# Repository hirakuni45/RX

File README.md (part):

Renesas RX Microcontroller
=========

[Japanese](READMEja.md)
   
## Overview
   
This is a program by Renesas RX microcontroller and its compiler rx-elf-gcc, g++.   
I am currently using Renesas GNU-RX gcc 8.3.0 as my main development tool.   
GNU-RX supports RXv3 and DFPU, and has excellent optimization.   

Currently, a dedicated writing program has been implemented that has been tested on Windows, OS-X, and Linux.   
Development is now possible in multiple environments.   

Currently supported and tested devices:   
|Series|MinV|MaxV|MHz|Core|FPU|TFU|DFPU|Operation check|rx_prog|Linker file|
|---|:-:|:-:|:-:|:-:|:-:|:-:|:-:|:-:|:-:|---|
|[RX110](RX110)|1.8|3.6|32|RXv1|－|－|－|||R5F51103/4/5|
|[RX111](RX111)|1.8|3.6|32|RXv1|－|－|－|||R5F51115/6/7|
|[RX113](RX113)|1.8|3.6|32|RXv1|－|－|－|||R5F51136/8|
|[RX130](RX130)|1.8|5.5|32|RXv1|－|－|－|||R5F51305/6|
|[RX140](RX140)|1.8|5.5|48|RXv2|Yes|－|－|〇|〇|R5F51403/5/6|
|[RX13T](RX13T)|2.7|5.5|32|RXv1|Yes|－|－|||R5F513T3/5|
|[RX14T](RX14T)|2.7|5.5|48|RXv2|Yes|V1|－|||R5F514T5|
|[RX210](RX210)|1.62|5.5|32|RXv1|－|－|－|||R5F52108/B|
|[RX220](RX220)|1.62|5.5|32|RXv1|－|－|－|〇|〇|R5F52206|
|[RX231](RX231)|1.8|5.5|54|RXv2|Yes|－|－|〇|〇|R5F52316/7/8|
|[RX23W](RX23W)|1.8|5.5|54|RXv2|Yes|－|－|||R5F523W7/8|
|[RX23T](RX23T)|2.7|5.5|40|RXv2|Yes|－|－|||R5F523T5|
|[RX24T](RX24T)|2.7|5.5|80|RXv2|Yes|－|－|〇|〇|R5F524T8/A|
|[RX24U](RX24U)|2.7|5.5|80|RXv2|Yes|－|－|||R5F524UB/E|
|[RX261](RX26x)|1.6|5.5|64|RXv3|Yes|－|－|〇|〇|R5F52618|
|[RX26T](RX26T)|2.7|5.5|120|RXv3|Yes|V2|－|〇|〇|R5F526TF|
|[RX621](RX62x)|2.7|3.6|100|RXv1|Yes|－|－|〇|〇|R5F56218|
|[RX62N](RX62x)|2.7|3.6|100|RXv1|Yes|－|－|〇|〇|R5F562N7/8|
|[RX631](RX63x)|2.7|3.6|100|RXv1|Yes|－|－|〇|〇|R5F5631F|
|[RX63N](RX63x)|2.7|3.6|100|RXv1|Yes|－|－|〇|〇|R5F563NE|
|[RX63T](RX63T)|3.3|5|100|RXv1|Yes|－|－|〇|〇|R5F563T6|
|[RX64M](RX64M)|2.7|3.6|120|RXv2|Yes|－|－|〇|〇|R5F564MF/G/J/L|
|[RX71M](RX71M)|2.7|3.6|240|RXv2|Yes|－|－|〇|〇|R5F571MF/G/J/L|
|[RX651](RX65x)|2.7|3.6|120|RXv2|Yes|－|－|〇|〇|R5F5651E|
|[RX65N](RX65x)|2.7|3.6|120|RXv2|Yes|－|－|〇|〇|R5F565NE|
|[RX66N](RX66N)|2.7|3.6|120|RXv3|Yes|V1|Yes|||R5F566ND/N|
|[RX660](RX660)|2.7|5.5|120|RXv3|Yes|－|－|||R5F56609|
|[RX671](RX671)|2.7|5.5|120|RXv3|Yes|－|－|||R5F5671C/E|
|[RX72N](RX72N)|2.7|3.6|240|RXv3|Yes|V1|Yes|〇|△|R5F572ND/N|
|[RX72M](RX72M)|2.7|3.6|240|RXv3|Yes|V1|Yes|△|△|R5F572MD/N|
|[RX66T](RX66T)|2.7|5.5|160|RXv3|Yes|－|－|〇|〇|R5F566TA/E/F/K|
|[RX72T](RX72T)|2.7|5.5|200|RXv3|Yes|V1|－|〇|〇|R5F572TF/K|
    
- The directory structure is updated daily.
- Some features are still under construction.
- The project consists of a Makefile and related headers and source code, and includes dedicated startup routines and linker scripts.

---
**Please make a request if you want us to support other RX devices. (Conditions below)**
- Become a support member of hirakuni45 GitHub.
- Lend us a board with the RX microcontroller you are requesting support for.
- You agree to release newly added files related to the RX microcontroller under the MIT license.

**If you do not know how to use the framework**
- Create a GitHub account and post in Discussions.
- You can also become a support member to get extensive support.

**If you have a problem with the framework or need a fix**, please create a Github account and post a note in Discussions.
- Create a Github account and post in Issues.
- If you have a modification request, post it in Discussions.
- If you have a pull request, please write the contents in Issues and Discussions in advance.

---

Space Invaders Emulator, NES Emulator, for RX65N/RX72N Envision kit   
    
WAV/MP3 Audio Player, File selector, for RX65N/RX72N Envision kit   
    
functional calculator, DX7 Emulator

YouTube: NES Emulator for RX65N Envision kit
   
Device control classes with template design patterns provide flexible and concise functionality.   
Due to its functionality, it does not require difficult or complicated settings or code generation by separate programs.   
   
```C++
// LED flashing program
#include "common/renesas.hpp"

namespace {
//  typedef device::PORT<device::PORT0, device::bitpos::B7> LED;  // LED connection port, Active HIGH
    typedef device::PORT<device::PORT0, device::bitpos::B7, false> LED;  // LED connection port, Active LOW
}

int main(int argc, char** argv);

int main(int argc, char** argv)
{
    SYSTEM_IO::boost_master_clock();

    LED::OUTPUT();
    while(1) {
        utils::delay::milli_second(250);
        LED::P = 1;
        utils::delay::milli_second(250);
        LED::P = 0;
    }
}
```
   
In order to complete the process from dependency rule generation to compilation and linking, usually with a single "make" command,
 I do not need it.   
No need for a dedicated boot program or loader I can write and execute.   
For development, we recommend using "Visual Studio Code" that can be used on multiple platforms.   
   
---

## RX Project, Library List

- For device I/O operations, dedicated headers are provided utilizing template class libraries implemented in C++.
- We also provide a full set of utilities and class libraries. 

|directory|contents|
|---|---|
|[all_project_build.sh](./all_project_build.sh)|build all projects (shell script) |
|[/RX110](./RX110)|RX110 specific device definition class, linker script|
|[/RX111](./RX111)|RX111 specific device definition class, linker script|
|[/RX130](./RX130)|RX130 specific device definition class, linker script|
|[/RX13T](./RX13T)|RX13T specific device definition class, linker script|
|[/RX14T](./RX14T)|RX14T specific device definition class, linker script|
|[/RX140](./RX140)|RX140 specific device definition class, linker script|
|[/RX210](./RX210)|RX210 specific device definition class, linker script|
|[/RX220](./RX220)|RX220 specific device definition class, linker script|
|[/RX231](./RX231)|RX231 specific device definition class, linker script|
|[/RX23W](./RX23W)|RX23W specific device definition class, linker script|
|[/RX23T](./RX23T)|RX23T specific device definition class, linker script|
|[/RX24T](./RX24T)|RX24T specific device definition class, linker script|
|[/RX24U](./RX24U)|RX24U specific device definition class, linker script|
|[/RX26x](./RX26x)|RX260/RX261 specific device definition class, linker script|
|[/RX26T](./RX26T)|RX26T specific device definition class, linker script|
|[/RX62x](./RX62x)|RX621/RX62N dedicated device definition class, linker script|
|[/RX63x](./RX63x)|RX631/RX63N specific device definition class, linker script|
|[/RX63T](./RX63T)|RX63T specific device definition class, linker script|
|[/RX64M](./RX64M)|RX64M dedicated device definition class, linker script|
|[/RX65x](./RX65x)|RX651/RX65N specific device definition class, linker script|
|[/RX660](./RX660)|RX660 specific device definition class, linker script|
|[/RX66N](./RX66N)|RX66N specific device definition class, linker script|
|[/RX66T](./RX66T)|RX66T dedicated device definition class, linker script|
|[/RX671](./RX671)|RX671 specific device definition class, linker script|
|[/RX71M](./RX71M)|RX71M dedicated device definition class, linker script|
|[/RX72N](./RX72N)|RX72N dedicated device definition class, linker script|
|[/RX72M](./RX72M)|RX72M dedicated device definition class, linker script|
|[/RX72T](./RX72T)|RX72T dedicated device definition class, linker script|
|[/RX600](./RX600)|RX microcontroller common device definition class|
|[/common](./common)|shared classes, headers, etc.|
|[/rxlib](./rxlib)|zlib, png, mad, gmp, mpfr libraries|
|[/FreeRTOS](./FreeRTOS)|FreeRTOS for various RX microcontrollers and simple samples|
|[/ff14](./ff14)|ChaN's fatfs source code and handler for RX microcontrollers|
|[/chip](./chip)|various device specific control driver libraries such as I2C, SPI, etc|
|[/graphics](./graphics)|Graphics drawing related classes|
|[/gui](./gui)|Graphics user interface related classes (GUI Widget)|
|[/sound](./sound)|sound and audio related classes|
|[/usb](./usb)|USB handler, manage class|
|[/tinyusb](./tinyusb)|TinyUSB source code|
|[/rxprog](./rxprog)|RX microcontroller, Flash program writing tool (for Windows, OS-X, Linux)
|[LICENSE](./LICENSE)|license description file|

---

## Sample Projects (Applications)

|Directory|RX220|RX631|RX63T|RX62N|RX24T|RX66T|RX72T|RX64M|RX71M|RX65N|RX72N|Contents|
|---------|:---:|:---:|:---:|:---:|:---:|:---:|:---:|:---:|:---:|:---:|:---:|---|
|[/FIRST_sample](./FIRST_sample)|〇|〇|〇|〇|〇|〇|〇|〇|〇|〇|〇|LED blinking Sample Program|
|[/SCI_sample](./SCI_sample)|〇|〇|〇|〇|〇|〇|〇|〇|〇|〇|〇|serial communication Sample Program|
|[/MTU_sample](./MTU_sample)|－|－|－|〇|〇|〇|〇|〇|〇|〇|〇|Multi-Function Timer Pulse Unit Sample Program|
|[/CAN_sample](./CAN_sample)|－|〇|－|〇|－|〇|〇|〇|〇|△|〇|CAN Communication Sample Program|
|[/FLASH_sample](./FLASH_sample)|－|－|－|－|〇|〇|〇|〇|〇|〇|〇|Internal data flash operation sample|
|[/FreeRTOS](./FreeRTOS)|〇|〇|－|〇|〇|〇|〇|〇|〇|〇|〇|FreeRTOS Basic operation sample|
|[/GPTW_sample](./GPTW_sample)|－|－|－|－|△|〇|〇|－|－|△|〇|GPTW PWM Sample Program|
|[/I2C_sample](./I2C_sample)|〇|〇|－|〇|〇|〇|〇|〇|〇|〇|〇|I2C Device Access Sample|
|[/RAYTRACER_sample](./RAYTRACER_sample)|－|〇|－|〇|〇|〇|〇|〇|〇|〇|〇|Ray Tracing Benchmark|
|[/SDCARD_sample](./SDCARD_sample)|－|－|－|－|〇|〇|〇|〇|△|〇|〇|SD Card Operation Sample|
|[/SIDE_sample](./SIDE_sample)|－|－|－|－|－|－|－|－|－|〇|〇|Envision Kit, Space Invaders emulator|
|[/NESEMU_sample](./NESEMU_sample)|－|－|－|－|－|－|－|－|－|〇|〇|Envision Kit, NES emulator|
|[/GUI_sample](./GUI_sample)|－|－|－|－|－|－|－|－|－|〇|〇|GUI Sample、Graphics User Interface (Soft rendering, using DRW2D engine)|
|[/AUDIO_sample](./AUDIO_sample)|－|－|－|－|－|－|－|〇|△|〇|〇|MP3/WAV Audio Player (FreeRTOS)|
|[/SYNTH_sample](./SYNTH_sample)|－|－|－|－|〇|〇|〇|〇|〇|〇|〇|FM sound synthesizer emulator|
|[/CALC_sample](./CALC_sample)|－|〇|－|〇|－|〇|〇|〇|〇|〇|〇|Function calculator samples (gmp, mpfr libraries)|
|[/DSOS_sample](./DSOS_sample)|－|－|－|－|－|－|－|－|－|△|〇|Digital Storage Oscilloscope Samples|
|[/PSG_sample](./PSG_sample)|－|〇|－|〇|－|〇|〇|〇|〇|〇|〇|Pseudo PSG Sound Source Performance Samples|
|[/TUSB_HOST_sample](./TUSB_HOST_sample/)|－|－|－|－|－|－|－|－|－|〇|〇|TinyUSB/Host Samples|

*Please consider directories and files that are not in the above list but exist when checked out as work in progress.

---

### rxlib directory

- Open source libraries built for RX microcontrollers

[rxlib](./rxlib) See also

---

### common directory

- Various utilities
- Convenience Classes
- Common files for each microcontrollers

[common](./common) See also

---

### chip directory

- Template driver classes for various IC manufacturers (I2C, SPI, and various other interfaces)
- In C++, the use of templates can be used to generalize operations using interfaces such as I2C and SPI.
- The headers in the chip directory are dedicated to the initialization and control of each IC and are not concerned with the interface definition.
- The context of the interface (control pins) is given by reference.
- Since there is no definition of interfaces, the creation is very versatile and highly flexible.

[chip](./chip) See also

---

### graphics directory

 - Classes related to screen rendering

[graphics](./graphics) See also

---

### gui directory

- GUI Widget Classes

[gui](./gui) See also

---

### sound directory

 - Classes related to sound

[sound](./sound) See also

---

### ff14 directory

- Mr. ChaN's FatFs source code set
- MMC Driver Class (SPI)
- If SDHI interface is available, real mode driver can also be selected.

[ff14](./ff14) See also

---

### KiCAD directory

- For KiCAD, parts files, etc.

[KiCAD_lib](./KiCAD_lib) See also

---

### legacy directory

- Files not currently supported, etc.

[legacy](./legacy) See also

---

## Installation and Feature Overview of Renesas GNU-RX (14.2.0-202607)

[Open Source Tools for Renesas](https://llvm-gcc-renesas.com/ja/) provides GNU tools for RX microcontrollers.

The latest (as of July 2026) GNU toolchain for RX microcontrollers—
- gcc 14.2.0 [released]
- binutils 2.44 [released]
- newlib 4.4.0 [released]
- gdb 16.2 [released]

A toolchain for RX microcontrollers based on these components is available for download.

Anyone can download these tools by registering, and there are no size limits.
Additionally, it appears they provide optimization for RX microcontrollers and support for the latest CPU cores.

**When installing, we recommend selecting “Available to all users”**

- Since gcc is based on version 14.2.0, it supports C++17
- It offers deeper optimization than standard gcc and supports the latest CPU cores
- All projects using the C++ frameworks published here can be compiled
- Experimental support for C++20 and C++26 features has been added
- Support is also provided by CyberTHOR Studios Limited
- To use this tool with MSYS2, after installing the toolchain, please set the command path in `.bash_profile`
- When compiling open-source libraries, there is an issue where the path string may contain “spaces” or double-byte characters
- To work around this issue, it is recommended to copy the directory to “/usr/local” and use that path
- Based on gcc-14, the installation directory has changed (when installed for use by all users)

```bash
# rx-elf path
# PATH=$PATH:/usr/local/rx-elf/bin
PATH=$PATH:/C/ProgramData/'GCC for Renesas RX 14.2.0.202607-GNURX-ELF'/rx-elf/rx-elf/bin
```

- RXv3 core support
- Generation of double-precision floating-point instructions for RX72N/RX72M
- Support for the built-in TFU (trigonometric function unit) in RX14T/RX26T/RX72T/RX72N/RX72M (V1/V2)

### Compiler options for TFUv1 and TFUv2

Starting with the gcc-14.2.0 base, the handling of the TFU has changed

```sh
TFUv1:
  -mtfu-version=v1 -mtfu=intrinsic,mathlib

TFUv2:
  -mtfu-version=v2 -mtfu=intrinsic,mathlib
```

These settings are configured in common/makefile

- The built-in functions differ between TFUv1 and TFUv2, so please be careful when using TFU
- When TFU usage is specified, the built-in variable “__TFU” is set to “TFUv1: 1” or “TFUv2: 2”

---

The difference between CC-RX:   
In terms of compiler optimization, CC-RX seems to be superior to GNU-RX in the CoreMark benchmark.   
It's hard to imagine why such a big difference would occur, but if you know the internal structure of the CPU, you might be able to achieve it...   
   
|Compiler|RX core|CoreMark (MHz)|Rate|
|---|:-:|:-:|:-:|
|CC-RX (V3.02)|RX72N|5.21|1.00|
|GNU-RX (8.3.x)|RX72N|3.59|0.69|
|||||
|CC-RX (V3.02)|RX65N|4.37|1.00|
|GNU-RX (8.3.x)|RX65N|3.22|0.74|
   
The above values are quite exciting, but when running actual applications, we do not feel such a big difference in sensory perception.   
- The big difference seems to occur in the case of applications that use a lot of instructions that require a relatively large number of CPU cycles, such as multiplication and division.   
- For applications that use a lot of floating point instructions, GNU-RX may be faster.
   
No matter how good CC-RX is, it's not worth the cost for hobbyists, and if it doesn't support C++11, it's not practical to use.   
In addition, the above benchmarks are based on CoreMark, so you need to evaluate it with actual applications to know what it really is.   
   
---
## RX Development environment preparation (Windows、MSYS2)
   
 - On Windows, install the MSYS2 environment in advance.   
 - MSYS2 has msys2, mingw32, mingw64 and 3 different environments, but gcc for RX microcontroller
   Because it is necessary to build of, do with msys2.   
1. MSYS2 is a UNIX-based application development environment.
2. MINGW32 is an environment for i686 that the exception model of gcc is not war related to SEH because of Borland patent.
3. MINGW64 is an environment for developing Windows-based applications.   
 - If you have installed any software other than Microsoft's anti-virus software, please disable it.
1. The GCC build may take an unusually long time or may fail to build.   

 - MSYS2 upgrade

```bash
   pacman -Sy pacman
   pacman -Syu
```
   
- Open the console again. (You should see a message as you reopen the console)   
   
```bash
   pacman -Su
```
- The update is done multiple times, then follow the instructions on the console.
- You need to reopen the console several times.

- Install gcc, texinfo, gmp, mpfr, mpc, diffutils, automake, zlib, tar, make, unzip, git commands etc
```bash
   pacman -S gcc
   pacman -S texinfo
   pacman -S mpc-devel
   pacman -S diffutils
   pacman -S automake
   pacman -S zlib
   pacman -S tar
   pacman -S make
   pacman -S unzip
   pacman -S zlib-devel
   pacman -S git
```
   
---
## RX Development environment preparation (OS-X)
   
- In OS-X, install macports in advance.   
  brew is not recommended because it has less flexibility   
- Depending on the version of OS-X, you may need to install X-Code, Command Line Tools, etc. in advance   
 - macports upgrade   
```bash
   sudo port -d self update
```
- As you probably know, in the early stage of OS-X, llvm starts by calling gcc.
- However, llvm can not currently build gcc cross compilers.
- So, I will install gcc on macports, I will use the 5 series version.
```bash
   sudo port install gcc5
   sudo ln -sf /opt/local/bin/gcc-mp-5  /usr/local/bin/gcc
   sudo ln -sf /opt/local/bin/g++-mp-5  /usr/local/bin/g++
   sudo ln -sf /opt/local/bin/g++-mp-5  /usr/local/bin/c++
```
- You may need to reboot.
- For now, please check.
```bash
   gcc --version
```
   
```bash
   gcc (MacPorts gcc5 5.4.0_0) 5.4.0
   Copyright (C) 2015 Free Software Foundation, Inc.
   This is free software; see the source for copying conditions.  There is NO
   warranty; not even for MERCHANTABILITY or FITNESS FOR A PARTICULAR PURPOSE.
```
   
 - Install texinfo, gmp, mpfr, mpc, diffutils, automake command etc
```bash
   sudo port install texinfo
   sudo port install gmp
   sudo port install mpfr
   sudo port install libmpc
   sudo port install diffutils
   sudo port install automake
```
   
---
## RX Development environment preparation (Ubuntu)

- There are multiple Linux environments, so here we will write the case for the "Ubuntu 16.04 LTS" environment.
   
- Install texinfo, gmp, mpfr, mpc, diffutils, automake command etc
```bash
   sudo apt-get install texinfo
   sudo apt-get install libgmp-dev
   sudo apt-get install libmpfr-dev
   sudo apt-get install libmpc-dev
   sudo apt-get install diffutils
   sudo apt-get install automake
   sudo apt-get install zlib1g-dev
```
   
---
## RX Development environment construction
   
- The RX compiler (rx-elf-gcc, g++) uses "gcc-7.5.0".   
- Download "binutils-2.34.tar.gz".   
- Download "gcc-7.5.0.tar.gz".   
- Download "newlib-2.4.0.tar.gz".   
- There are multiple versions of binutils, gcc and newlib, but some combinations   
  It has been found that ineligible binaries (which have subtle problems with operation) will be built.
- This bug occurs when using Renesas network stack (net_T4).
- It is not possible to identify the cause why such malfunction occurs.
- Here is a list of combinations that we have investigated.
```
   binutils-2.27, gcc-4.9.4, newlib-2.2.0 ---> OK
   binutils-2.27, gcc-5.5.0, newlib-2.2.0 ---> OK
   binutils-2.27, gcc-5.5.0, newlib-2.4.0 ---> OK
   binutils-2.27, gcc-6.4.0, newlib-2.4.0 ---> OK
   binutils-2.28, gcc-6.4.0, newlib-2.4.0 ---> OK
   binutils-2.30, gcc-6.4.0, newlib-2.4.0 ---> OK (old current)
   binutils-2.30, gcc-6.4.0, newlib-3.0.0 ---> NG
   binutils-2.34, gcc-7.5.0, newlib-2.4.0 ---> OK (new current)
```
- Using the latest gcc seems to be faster code, especially for C++.
   
---
#### build binutils-2.34
```bash
   cd
   tar xfvz binutils-2.34.tar.gz
   cd binutils-2.34
   mkdir rx_build
   cd rx_build
   ../configure --target=rx-elf --prefix=/usr/local/rx-elf --disable-nls
   make
   make install     OS-X,Linux: (sudo make install)
```

-  Pass PATH to /usr/local/rx-elf/bin (edit .bash_profile and add path)

```bash
   PATH=$PATH:/usr/local/rx-elf/bin
```

- Open the console again.

```bash
   rx-elf-as --version
```

- Execute the assembler command and check if the path is valid.
  
#### Build C compiler
```bash
    cd
    tar xfvz gcc-7.5.0.tar.gz
    cd gcc-7.5.0
    mkdir rx_build
	cd rx_build
    ../configure --prefix=/usr/local/rx-elf --target=rx-elf --enable-languages=c --disable-libssp --with-newlib --disable-nls --disable-threads --disable-libgomp --disable-libmudflap --disable-libstdcxx-pch --disable-multilib --enable-lto
    make
    make install     OS-X,Linux: (sudo make install)
```
  
#### Build newlib
```bash
    cd
    tar xfvz newlib-2.4.0.tar.gz
	cd newlib-2.4.0
    mkdir rx_build
    cd rx_build
    ../configure --target=rx-elf --prefix=/usr/local/rx-elf
	make
    make install     OS-X: (sudo make install)
```
- In Linux environment, sudo command does not recognize the path of binutils set up locally.
"Make install" will fail, so write the following script and execute it.
```bash
#!/bin/sh
# file: rx_install.sh

PATH=${PATH}:/usr/local/rx-elf/bin
make install
```
   
```bash
    sudo rx_install.sh
```
   
#### Build C++ compiler
```bash
    cd
    cd gcc-7.5.0
    cd rx_build
    ../configure --prefix=/usr/local/rx-elf --target=rx-elf --enable-languages=c,c++ --disable-libssp --with-newlib --disable-nls --disable-threads --disable-libgomp --disable-libmudflap --disable-libstdcxx-pch --disable-multilib --enable-lto --with-system-zlib
    make
    make install     OS-X,Linux: (sudo make install)
```
---
   
 - The built compiler collection is listed in the link below. (MSYS2 only)   
http://www.rvf-rc45.net/Renesas_GNU_Tools/ 

---
## Get RX Framework Source Code
```bash
    git clone https://github.com/hirakuni45/RX.git
```
   
---
### Boost installation used by RX framework

- In the past, boost was installed for mingw64 using pacman in the MSYS2 environment.
- However, as the version of boost advanced, we found that this boost caused problems.
- Therefore, we put the boost archive in the proper location and handle it.
- This method is used in the MSYS2 environment.
- Since boost uses 1.74.0, please download it in advance (place it in D:³ Download). (boost_1_74_0.tar.gz)

```bash
cd /c/
tar xfvz /d/Download/boost_1_74_0.tar.gz
```

---
## RX Build all projects
```bash
    sh all_project_build.sh [clean]
```
--- 
## How to write program to RX microcontroller

There are several ways, but the easiest and least expensive way is to use the serial interface
It is a method of writing.   
- However, the writing speed is not very fast.   
   
In case of RX microcontroller with built-in USB interface, you can boot and connect with USB, but the driver Seems to only support the Windows version.
- The circumstances around here may be wrong as we have not investigated in detail.   
   
The most common, because not all RX microcontrollers have built-in USB interface We will show you how to write using serial interface.
   
- Writing at the serial interface is reasonably fast but easy and secure, and easy to connect.   
   
- The hardware manual describes the connection with the serial port and switching to boot mode.
  Please refer to it.   
- Normally, setting MD terminal to L or H allows switching between program and internal ROM execution.   
- It is also necessary to control the state of the UB terminal.   
- If you use a USB serial conversion module etc., it is easy to get power.   

1. RXD serial reception   
2. TXD serial transmission   
3. VCC power (5V or 3.3V)   
4. GND power 0V   
- As 3.3V can only extract a limited current, a regulator is always required.   
- Details on the connection method, boot mode settings, etc. can be found in the hardware manual for each device.   
   
## Construction of flash programmer for RX microcontroller
- Currently, flash writing to RX63T, RX24T, RX64M, and RX71M is confirmed.
- Since the reset is not controlled, it is necessary to assert the reset signal at the time of writing.
- In the current version, only erase, write and compare operations are implemented.
- Code protection ID settings and operations are not implemented yet.
- In the RX24T and RX63T, the erase operation is ignored because the erase is performed automatically when the connection is established.
   
- Build rxprog in MSYS2 environment.
- Copy the built executable file to "/usr/local/bin".
- Pass the PATH to /usr/local/bin.
```bash
    cd rxprog
    make
    make install
```
```
Renesas RX Series Programmer Version 0.90b
Copyright (C) 2016,2018 Hiramatsu Kunihito (hira@rvf-rc45.net)
usage:
rx_prog [options] [mot file] ...

Options :
    -P PORT,   --port=PORT     Specify serial port
    -s SPEED,  --speed=SPEED   Specify serial speed
    -d DEVICE, --device=DEVICE Specify device name
    -e, --erase                Perform a device erase to a minimum
    -v, --verify               Perform data verify
    -w, --write                Perform data write
    --progress                 display Progress output
    --device-list              Display device list
    --verbose                  Verbose output
    -h, --help                 Display this
```
- Edit rx_prog.conf and set the COM port to connect and the baud rate.
- Ports and baud rates can be set for each of Windows, OS-X and Linux environments.
- You can write a standard serial port in "rx_prog.conf", and you should set it according to your environment.
- Each project's "Makefile" contains a script that can be written using "make run".
   
rx_prog.conf:
```
port_win   = COM12
port_osx   = /dev/tty.usbserial-DA00X2QP
port_linux = /dev/ttyUSB0
speed_win = 230400
speed_osx = 230400
speed_linux = 230400
```
---
## Development using Renesus RX72N Envision Kit

---
## Programming environment using C++ framework
   
- The following is an example program to communicate with SCI in C++.   
1. The port of SCI is defined by "port_map.hpp", and there is more than one port to select
There is no need to make complicated settings if you set "second candidate" or "third candidate".   
2. The baud rate can be set as an integer, and is automatically calculated internally from the set frequency.   
3. Even if you use interrupts, you can use them without polling (polling).   
4. Transmission and reception are performed through a fixed length FIFO class, and the size can be freely defined.   
5. The sci_putch and sci_getch functions are called from POSIX file functions, so they can be linked externally.   
6. The above functions are accessed from stdout, stdin, stderr descriptors, so you can also use the printf function, but for various reasons we do not recommend using "utils :: format", which is the size It is smaller, more flexible, convenient and safe.   
```C++
#include "common/renesas.hpp"
#include "common/fixed_fifo.hpp"
#include "common/sci_io.hpp"
#include "common/format.hpp"

namespace {
//  Use SCI9
    typedef device::SCI9 SCI_CH;

    typedef utils::fixed_fifo<char, 512> RXB;  // RX (RECV) buffer definition at 512 bytes
    typedef utils::fixed_fifo<char, 256> TXB;  // TX (SEND) buffer definition at 256 bytes

    typedef device::sci_io<SCI_CH, RXB, TXB> SCI;
//    When selecting a second candidate for the SCI port
//    typedef device::sci_io<SCI_CH, RXB, TXB, device::port_map::option::SECOND> SCI;
    SCI     sci_;
}

extern "C" {
    // standard output, called from "syscalls.c"（stdout, stderr）
    void sci_putch(char ch) { sci_.putch(ch); }

    void sci_puts(const char* str) { sci_.puts(str); }

    // standard input, called from "syscalls.c"（stdin）
    char sci_getch(void) { return sci_.getch(); }

    uint16_t sci_length() { return sci_.recv_length(); }
}

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
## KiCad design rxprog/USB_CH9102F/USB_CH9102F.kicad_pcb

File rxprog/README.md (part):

Renesas RX microcontroller flash programming tool (rx_prog)
=========

[Japanese](READMEja.md)

## Overview
Tool to write program to flash memory of RX microcontroller using serial interface   
   
|RX Microcontroller|Support|operation verification|
|:-:|:-:|:-:|
|RX13T|〇|ー|
|RX140|〇|〇|
|RX220|〇|〇|
|RX230|〇|ー|
|RX231|〇|〇|
|RX23T|〇|ー|
|RX24T|〇|〇|
|RX24U|〇|ー|
|RX260/RX261|〇|ー|
|RX26T|〇|〇|
|RX621/RX62N|〇|〇|
|RX631/RX63N|〇|〇|
|RX63T|〇|〇|
|RX64M|〇|〇|
|RX651/RX65N|〇|ー|
|RX66T|〇|〇|
|RX71M|〇|〇|
|RX72T|〇|〇|
|RX72N|〇|ー|
   
---
   
## Project list
   
- main.cpp
- conf_in.hpp
- file_io.cpp
- file_io.hpp
- format.hpp
- motsx_io.hpp
- protocol_base.hpp
- rs232c_io.hpp
- rx_prog.hpp
- rx_protocol.hpp
- rx220_protocol.hpp
- rx23x_protocol.hpp
- rx24t_protocol.hpp
- rx26t_protocol.hpp
- rx62x_protocol.hpp
- rx63x_protocol.hpp
- rx64m_protocol.hpp
- rx65x_protocol.hpp
- rx66t_protocol.hpp
- rx72t_protocol.hpp
- sjis_utf16.cpp
- sjis_utf16.hpp
- string_utils.cpp
- string_utils.hpp
- Makefile
- rx_prog.conf
- /USB_CH9102F
- /USB_CP2102N
   
---
   
## Preparation of build (compilation) environment (Windows)
   
- MSYS2 setup
- gcc related installation (C++20)
- With C++20 support, Boost is no longer required
   
See development environment preparation of 'RX/README.md'
   
---
   
## Build method, environment setting
   
- make
- Copy configuration file and executable file by make install
- pass the path to '/usr/local/bin'
   
---
   
## Connection preparation (serial connection)
   
- Connect the VSS pin of the microcontroller to the GND of USB serial.
- Connect the RXD1 pin on the microcontroller side with the USB serial TXD.
- Connect the TXD1 pin on the microcontroller side with the USB serial RXD.
※SCI port at boot (usually SCI1, hardware manual for confirmation)   
- Pull down if the device has a UB terminal. (4.7K)
- Pull down if there is an EMLE terminal. (4.7K)
- Set the MD terminal to "Low" and input the "Reset" signal.
- When executing an internal program, set the MD pin to "High level" and input reset signal.
- MDE(13) is 0 (assumed little-endian)

---

## Connection terminal list

### RX140:

|Terminal|LFQFP 64|
|---|---|
|MD|MD(3)|
|RXD|P30/RXD1(14)|
|TXD|P26/TXD1(16)|

|Mode|MD|
|---|:---:|
|Serial Boot|0|
|Single Chip|1|

VCL: 4.7uF

### RX220:
|Terminal|LFQFP 64|
|---|---|
|MD|MD(3)|
|B/UB|PC7(27)|
|RXD|P30/RXD1(14)|
|TXD|P26/TXD1(16)|

|Mode|B/UB|MD|
|---|:---:|:---:|
|Boot Mode|0|0|
|User Boot Mode|1|0|
|Single Chip|-|1|

VCL: 0.1uF

---
### RX231:   
|Terminal|LFQFP 64|LFQFP 100|
|---|---|---|
|MD|MD(3)|MD(7)|
|UB|PC7(27)|PC7(45)|
|RXD|P30/RXD1(14)|P30/RXD1(20)|
|TXD|P26/TXD1(16)|P25/TXD1(23)|

|Mode|UB|MD|
|---|:---:|:---:|
|Serial Boot|0|0|
|USB Boot|1|0|
|Single Chip|-|1|

VCL: 4.7uF

---
### RX621/RX62N:
|Terminal|RX621/RX62N (144)|
|---|---|
|MD0|MD0(16)|
|MD1|MD1(15)|
|EMLE|EMLE(10)|
|RXD|P30/RXD1(29)|
|TXD|P26/TXD1(31)|
   
|Mode|MD0|MD1|
|---|:---:|:---:|
|Serial Boot|1|0|
|USB Boot|0|1|
|Single Chip|1|1|

VCL: 0.1uF

---
### RX631/RX63N:
|Terminal|LQFP 48|LQFP 64|TFLGA 64|LQFP 100|TFLGA 100|LQFP 144|TFLGA 145|LQFP 176|LFBGA 176|TFLGA 177|
|---|---|---|---|---|---|---|---|---|---|---|
|UB|PC7(21)|PC7(27)|PA6(D5)|PC7(45)|PC7(H7)|PC7(60)|PC7(N9)|PC7(76)|PC7(N10)|PC7(N10)|
|MD|MD/FINED(2)|MD/FINED(3)|MD/FINED(C2)|MD/FINED(7)|MD/FINED(D3)|MD/FINED(16)|MD/FINED(G3)|MD/FINED(18)|MD/FINED(G3)|MD/FINED(G3)|
|EMLE|-|EMLE(1)|EMLE(C3)|EMLE(2)|EMLE(B1)|EMLE(10)|EMLE(E4)|EMLE(10)|EMLE(E2)|EMLE(E2)|
|RXD|P30/RXD1(10)|P30/RXD1(14)|P30/RXD1(E3)|P30/RXD1(20)|P30/RXD1(G3)|P30/RXD1(29)|P30/RXD1(J4)|PF2/RXD1(31)|PF2/RXD1(K3)|PF2/RXD1(K3)|
|TXD|P26/TXD1(12)|P26/TXD1(16)|P26/TXD1(G2)|P26/TXD1(22)|P26/RXD1(H1)|P26/RXD1(31)|P26/RXD1(K2)|PF0/RXD1(35)|PF0/RXD1(L3)|PF0/RXD1(L3)|

|Mode|UB|MD|
|---|:---:|:---:|
|Serial Boot|0|0|
|USB Boot|1|0|
|Single Chip|-|1|

VCL: 0.1uF

---
### RX63T/RX24T/RX26T/RX66T/RX72T:
|Terminal|RX63T (64)|RX24T (100)|RX26T (100)|RX66T (100)|RX72T (144)|
|---|---|---|---|---|---|
|VCL|0.1uF|4.7uF|0.47uF|0.47uF|0.47uF|0.47uF|
|UB|P00(2)|ー|ー|UB/P00(4)|UB/P00(9)|
|MD|MD(5)|MD(6)|MD/FINED(6)|MD/FINED(6)|MD/FINED(11)|
|EMLE|EMLE(1)|ー|EMLE(2)|EMLE(2)|EMLE(7)|
|RXD|PD5/RXD1(14)|PD5/RXD1(20)|PD5/RXD1(20)|PD5/RXD1(20)|PD5/RXD1(25)|
|TXD|PD3/TXD1(16)|PD3/TXD1(22)|PD3/TXD1(22)|PD3/TXD1(22)|PD3/TXD1(27)|

|Mode|UB|MD|
|---|:---:|:---:|
|Serial Boot|0|0|
|USB Boot|1|0|
|Single Chip|-|1|

---
### RX64M/RX71M/RX651/RX65N:
|Terminal|RX64M (176)|RX71M (176)|RX651/RX65N (176)|
|---|---|---|---|
|VCL|0.1uF|0.22uF|0.22uF|
|UB|PC7/UB(76)|PC7/UB(76)|PC7/UB(76)|
|MD|MD/FINED(18)|MD/FINED(18)|MD/FINED(18)|
|EMLE|EMLE(10)|EMLE(10)|EMLE(10)|
|RXD|PF2/RXD1(31)|PF2/RXD1(31)|PF2/RXD1(31)|
|TXD|PF0/TXD1(35)|PF0/TXD1(35)|PF0/TXD1(35)|
   
|Mode|UB|MD|
|---|:---:|:---:|
|Serial Boot|0|0|
|USB Boot|1|0|
|Single Chip|-|1|

---
### RX660/RX671:
|Terminal|RX660 (144)|RX671 (144)|
|---|---|---|
|UB|PC7/UB(60)|PC7/UB(60)|
|MD|MD/PN6(16)|MD(16)|
|RXD|P30/RXD1(29)|P30/RXD1(29)|
|TXD|P26/TXD1(31)|P26/TXD1(31)|

RX660:
|Mode|UB|MD|
|---|:---:|:---:|
|Serial Boot|0|0|
|User Boot|1|0|
|Single Chip|-|1|

VCL: 0.47uF

RX660: USB boot not available due to lack of USB interface

RX671:
|Mode|UB|MD|
|---|:---:|:---:|
|Serial Boot|0|0|
|USB Boot|1|0|
|Single Chip|-|1|

VCL: 0.22uF

---
   
- MD0、MD1、UB、MD、B/UB, and EMLE terminals are pulled up or down with a resistor (approximately 4.7K).
- Connect appropriate crystals to XTAL and EXTAL.
- Connect the specified capacitor to VCL.
- Connect all the power supplies such as VSS, VCC, AVSS, AVCC etc.
- Connect USB power sources such as USB_VSS and USB_VCC properly.
   
※For details, refer to the hardware manual for each device, "Overview, Pin Assignment", "Flash Memory, Boot Mode".   
※The circuit diagram of the Renesas board is available for reference.   
   
---
## Method of operation

### Confirm start of rx_prog
 - Run rx_prog and verify that it works (help is listed)
```
% rx_prog
Renesas RX Series Programmer Version 1.98
Copyright (C) 2016, 2026 Hiramatsu Kunihito (hira@rvf-rc45.net)
usage:
rx_prog [options] [mot file] ...

Options :
    -P PORT,   --port=PORT     Specify serial port
    -s SPEED,  --speed=SPEED   Specify serial speed
    -d DEVICE, --device=DEVICE Specify device name
    -e, --erase                Perform a device erase to a minimum
    --id=ID[:,]ID[:,] ...      Specify protect ID (16 bytes)
    -r, --read                 Perform data read
	--area=ORG[:,]END          Specify read area
    -v, --verify               Perform data verify
    -w, --write                Perform data write
    --progress                 display Progress output
    --erase-page-wait=WAIT     Delay per read page  (2000) [uS]
    --write-page-wait=WAIT     Delay per write page (5000) [uS]
    --device-list              Display device list
    --verbose                  Verbose output
    -h, --help                 Display this
```
   
### rx_prog.conf settings
 - Describe the settings of each device, port, baud rate, and so on.
 - You can specify the serial device port path individually so that settings can be shared between platforms.
 - Set the port name, baud rate, etc. according to your environment.
 - For the RX62x, the error is limited to 115200 for high baud rates.
   
rx_prog.conf configuration example
```
# Standard serial port, platform dependent port name
# port_win, port_osx and port_linux are recognized by platform and take precedence over port.
#port = /dev/ttyS10
#port = COM12
port_win   = COM3
port_osx   = /dev/tty.usbserial-DA00X2QP
port_linux = /dev/ttyUSB0

# Standard serial speed, platform dependent speed
# speed_win, speed_osx and speed_linux are recognized by platform and take precedence over speed.
# ※The maximum speed that can be set varies depending on the platform.
#speed = 230400
speed_win = 230400
speed_osx = 230400
speed_linux = 230400

# erase-page command wait [uS]
erase_page_wait = 2000
# write-page command wait [uS]
write_page_wait = 5000
```
rx_prog.conf is scanned and loaded in the following order:   
- Current directory
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
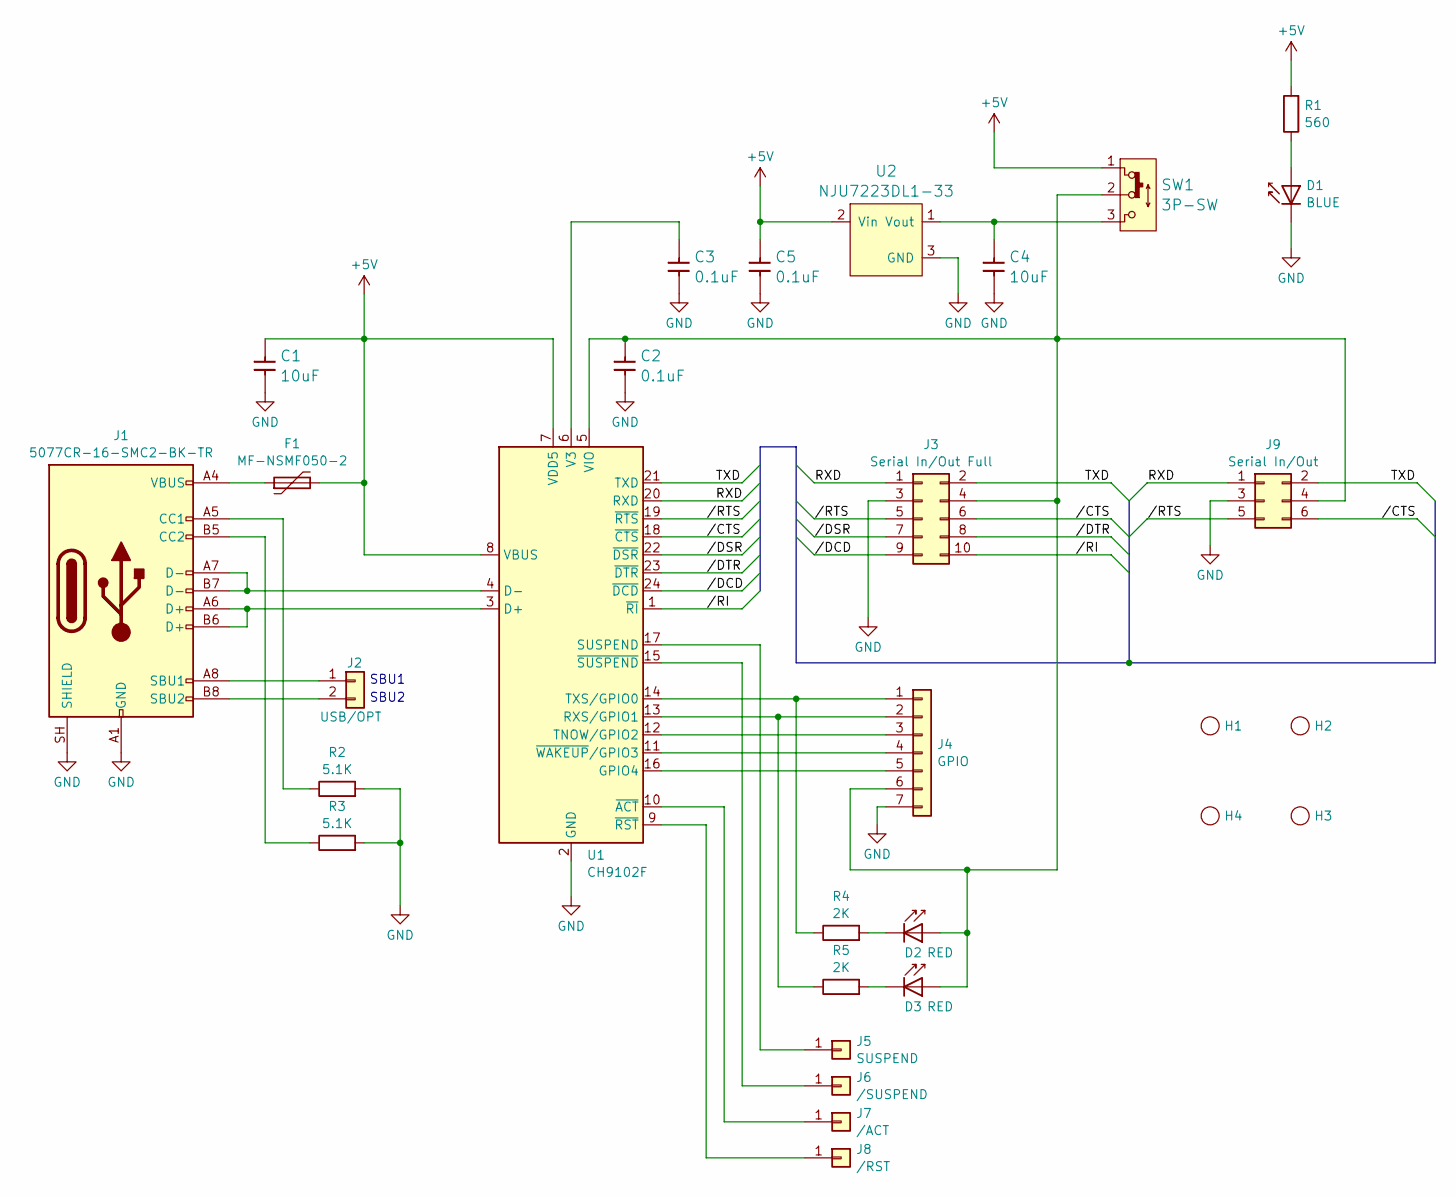
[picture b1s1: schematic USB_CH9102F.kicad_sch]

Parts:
C1, C4: 10uF; C_0603_1608Metric_Pad1.08x0.95mm_HandSolder
C2, C3, C5: 0.1uF; C_0603_1608Metric_Pad1.08x0.95mm_HandSolder
D1: BLUE; LED_0805_2012Metric_Pad1.15x1.40mm_HandSolder
D2, D3: RED; LED_0603_1608Metric_Pad1.05x0.95mm_HandSolder
F1: MF-NSMF050-2; Fuse_1206_3216Metric_Pad1.42x1.75mm_HandSolder
H1, H2, H3, H4: Hole3.2mm
J1: 5077CR-16-SMC2-BK-TR; USB_C_Receptacle_HCTL_HC-TYPE-C-16P-01A
J2: USB/OPT; PinHeader_1x02_P2.54mm_Vertical
J3: Serial In/Out Full; IDC-Header_2x05_P2.54mm_Vertical
J4: GPIO; PinHeader_1x07_P2.54mm_Vertical
J5: SUSPEND; PinHeader_1x01_P2.54mm_Vertical
J6: /SUSPEND; PinHeader_1x01_P2.54mm_Vertical
J7: /ACT; PinHeader_1x01_P2.54mm_Vertical
J8: /RST; PinHeader_1x01_P2.54mm_Vertical
J9: Serial In/Out; IDC-Header_2x03_P2.54mm_Vertical
R1: 560; R_0603_1608Metric_Pad0.98x0.95mm_HandSolder
R2, R3: 5.1K; R_0603_1608Metric_Pad0.98x0.95mm_HandSolder
R4, R5: 2K; R_0603_1608Metric_Pad0.98x0.95mm_HandSolder
SW1: 3P-SW; PinHeader_1x03_P2.54mm_Vertical
U1: CH9102F; QFN-24-1EP_4x4mm_P0.5mm_EP2.6x2.6mm
U2: NJU7223DL1-33; TO-252-2

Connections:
+5V: C1.2, C5.2, F1.2, R1.2, SW1.1, U1.7 (VDD5), U1.8 (VBUS), U2.2 (Vin)
/RXD: J3.1, J9.1, U1.20 (RXD)
/TXD: J3.2, J9.2, U1.21 (TXD)
//CTS: J3.6, J9.6, U1.18 (~CTS)
//DCD: J3.9, U1.24 (~DCD)
//DSR: J3.7, U1.22 (~DSR)
//DTR: J3.8, U1.23 (~DTR)
//RI: J3.10, U1.1 (~RI)
//RTS: J3.5, J9.5, U1.19 (~RTS)
GND: C1.1, C2.1, C3.1, C4.1, C5.1, D1.1 (K), J1.A1 (GND), J1.A12 (GND), J1.B1 (GND), J1.B12 (GND), J1.SH (SHIELD), J3.3, J4.7, J9.3, R2.2, R3.2, U1.2 (GND), U1.25 (GND), U2.3 (GND)
unnamed: D1.2 (A), R1.1
unnamed: C2.2, D2.2 (A), D3.2 (A), J3.4, J4.6, J9.4, SW1.2, U1.5 (VIO)
unnamed: D2.1 (K), R4.2
unnamed: D3.1 (K), R5.2
unnamed: F1.1, J1.A4 (VBUS), J1.A9 (VBUS), J1.B4 (VBUS), J1.B9 (VBUS)
unnamed: J1.A5 (CC1), R2.1
unnamed: J1.B5 (CC2), R3.1
unnamed: J1.A8 (SBU1), J2.1
unnamed: J1.B8 (SBU2), J2.2
unnamed: J4.1, R4.1, U1.14 (TXS/GPIO0)
unnamed: J4.2, R5.1, U1.13 (RXS/GPIO1)
unnamed: J4.3, U1.12 (TNOW/GPIO2)
unnamed: J4.4, U1.11 (~WAKEUP/GPIO3)
unnamed: J4.5, U1.16 (GPIO4)
unnamed: J5.1 (Pin_1_1), U1.17 (SUSPEND)
unnamed: J6.1 (Pin_1_1), U1.15 (~SUSPEND)
unnamed: J7.1 (Pin_1_1), U1.10 (~ACT)
unnamed: J8.1 (Pin_1_1), U1.9 (~RST)
unnamed: J1.A6 (D+), J1.B6 (D+), U1.3 (D+)
unnamed: J1.A7 (D-), J1.B7 (D-), U1.4 (D-)
unnamed: C3.2, U1.6 (V3)
unnamed: C4.2, SW1.3, U2.1 (Vout)

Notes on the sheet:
SBU2
SBU1

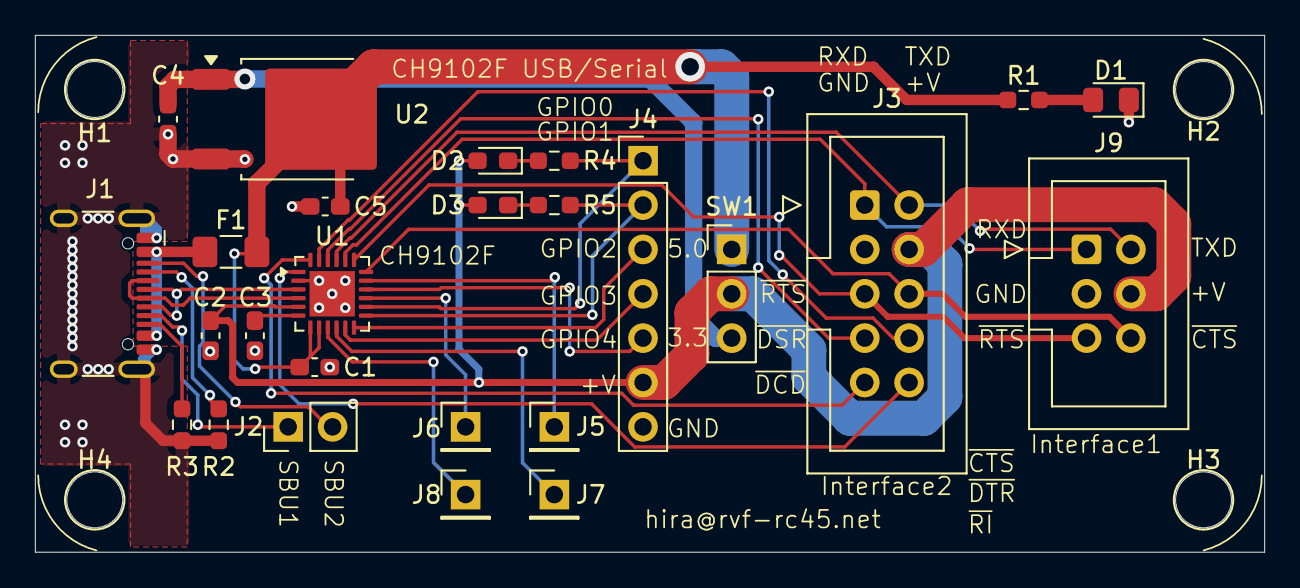
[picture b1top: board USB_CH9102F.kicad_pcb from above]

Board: 2 copper layers, 70.4 x 29.6 mm, 30 parts (0 on the bottom side), 32 nets.

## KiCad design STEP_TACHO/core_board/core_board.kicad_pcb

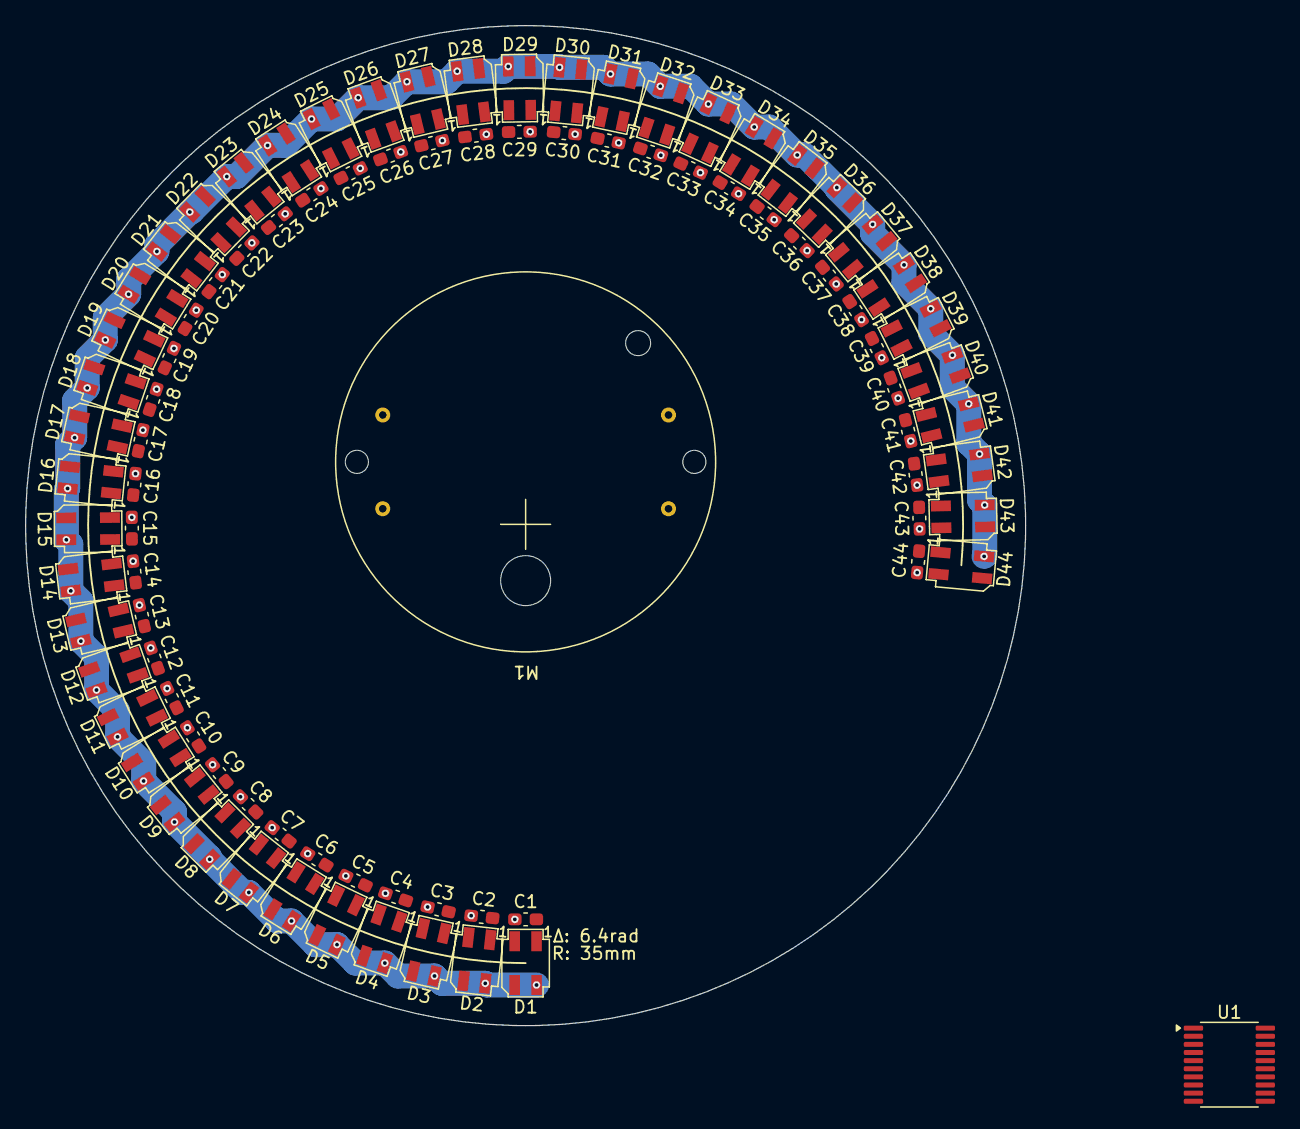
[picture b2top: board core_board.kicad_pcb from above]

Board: 2 copper layers, 80.0 x 80.0 mm, 90 parts (0 on the bottom side), 49 nets.

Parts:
C1, C2, C3, C4, C5, C6, C7, C8, C9, C10, C11, C12, C13, C14, C15, C16, C17, C18, C19, C20, C21, C22, C23, C24, C25, C26, C27, C28, C29, C30, C31, C32, C33, C34, C35, C36, C37, C38, C39, C40, C41, C42, C43, C44: 0.1uF; C_0603_1608Metric_Pad1.08x0.95mm_HandSolder
D1, D2, D3, D4, D5, D6, D7, D8, D9, D10, D11, D12, D13, D14, D15, D16, D17, D18, D19, D20, D21, D22, D23, D24, D25, D26, D27, D28, D29, D30, D31, D32, D33, D34, D35, D36, D37, D38, D39, D40, D41, D42, D43, D44: SK6812MINI; LED_SK6812MINI_PLCC4_3.5x3.5mm_P1.75mm_TITE
M1: X27.168
U1: TB6608FNG; SSOP-20_4.4x6.5mm_P0.65mm

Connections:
+5V: C1.2, C2.2, C3.2, C4.2, C5.2, C6.2, C7.2, C8.2, C9.2, C10.2, C11.2, C12.2, C13.2, C14.2, C15.2, C16.2, C17.2, C18.2, C19.2, C20.2, C21.2, C22.2, C23.2, C24.2, C25.2, C26.2, C27.2, C28.2, C29.2, C30.2, C31.2, C32.2, C33.2, C34.2, C35.2, C36.2, C37.2, C38.2, C39.2, C40.2, C41.2, C42.2, C43.2, C44.2, D1.4 (VDD), D2.4 (VDD), D3.4 (VDD), D4.4 (VDD), D5.4 (VDD), D6.4 (VDD), D7.4 (VDD), D8.4 (VDD), D9.4 (VDD), D10.4 (VDD), D11.4 (VDD), D12.4 (VDD), D13.4 (VDD), D14.4 (VDD), D15.4 (VDD), D16.4 (VDD), D17.4 (VDD), D18.4 (VDD), D19.4 (VDD), D20.4 (VDD), D21.4 (VDD), D22.4 (VDD), D23.4 (VDD), D24.4 (VDD), D25.4 (VDD), D26.4 (VDD), D27.4 (VDD), D28.4 (VDD), D29.4 (VDD), D30.4 (VDD), D31.4 (VDD), D32.4 (VDD), D33.4 (VDD), D34.4 (VDD), D35.4 (VDD), D36.4 (VDD), D37.4 (VDD), D38.4 (VDD), D39.4 (VDD), D40.4 (VDD), D41.4 (VDD), D42.4 (VDD), D43.4 (VDD), D44.4 (VDD), U1.6 (VM)
GND: C1.1, C2.1, C3.1, C4.1, C5.1, C6.1, C7.1, C8.1, C9.1, C10.1, C11.1, C12.1, C13.1, C14.1, C15.1, C16.1, C17.1, C18.1, C19.1, C20.1, C21.1, C22.1, C23.1, C24.1, C25.1, C26.1, C27.1, C28.1, C29.1, C30.1, C31.1, C32.1, C33.1, C34.1, C35.1, C36.1, C37.1, C38.1, C39.1, C40.1, C41.1, C42.1, C43.1, C44.1, D1.2 (VSS), D2.2 (VSS), D3.2 (VSS), D4.2 (VSS), D5.2 (VSS), D6.2 (VSS), D7.2 (VSS), D8.2 (VSS), D9.2 (VSS), D10.2 (VSS), D11.2 (VSS), D12.2 (VSS), D13.2 (VSS), D14.2 (VSS), D15.2 (VSS), D16.2 (VSS), D17.2 (VSS), D18.2 (VSS), D19.2 (VSS), D20.2 (VSS), D21.2 (VSS), D22.2 (VSS), D23.2 (VSS), D24.2 (VSS), D25.2 (VSS), D26.2 (VSS), D27.2 (VSS), D28.2 (VSS), D29.2 (VSS), D30.2 (VSS), D31.2 (VSS), D32.2 (VSS), D33.2 (VSS), D34.2 (VSS), D35.2 (VSS), D36.2 (VSS), D37.2 (VSS), D38.2 (VSS), D39.2 (VSS), D40.2 (VSS), D41.2 (VSS), D42.2 (VSS), D43.2 (VSS), D44.2 (VSS), U1.15 (GND), U1.17 (TQ)
unnamed: D1.1 (DOUT), D2.3 (DIN)
unnamed: D2.1 (DOUT), D3.3 (DIN)
unnamed: D3.1 (DOUT), D4.3 (DIN)
unnamed: D4.1 (DOUT), D5.3 (DIN)
unnamed: D5.1 (DOUT), D6.3 (DIN)
unnamed: D6.1 (DOUT), D7.3 (DIN)
unnamed: D7.1 (DOUT), D8.3 (DIN)
unnamed: D8.1 (DOUT), D9.3 (DIN)
unnamed: D9.1 (DOUT), D10.3 (DIN)
unnamed: D10.1 (DOUT), D11.3 (DIN)
unnamed: D11.1 (DOUT), D12.3 (DIN)
unnamed: D12.1 (DOUT), D13.3 (DIN)
unnamed: D13.1 (DOUT), D14.3 (DIN)
unnamed: D14.1 (DOUT), D15.3 (DIN)
unnamed: D15.1 (DOUT), D16.3 (DIN)
unnamed: D16.1 (DOUT), D17.3 (DIN)
unnamed: D17.1 (DOUT), D18.3 (DIN)
unnamed: D18.1 (DOUT), D19.3 (DIN)
unnamed: D19.1 (DOUT), D20.3 (DIN)
unnamed: D20.1 (DOUT), D21.3 (DIN)
unnamed: D21.1 (DOUT), D22.3 (DIN)
unnamed: D22.1 (DOUT), D23.3 (DIN)
unnamed: D23.1 (DOUT), D24.3 (DIN)
unnamed: D24.1 (DOUT), D25.3 (DIN)
unnamed: D25.1 (DOUT), D26.3 (DIN)
unnamed: D26.1 (DOUT), D27.3 (DIN)
unnamed: D27.1 (DOUT), D28.3 (DIN)
unnamed: D28.1 (DOUT), D29.3 (DIN)
unnamed: D29.1 (DOUT), D30.3 (DIN)
unnamed: D30.1 (DOUT), D31.3 (DIN)
unnamed: D31.1 (DOUT), D32.3 (DIN)
unnamed: D32.1 (DOUT), D33.3 (DIN)
unnamed: D33.1 (DOUT), D34.3 (DIN)
unnamed: D34.1 (DOUT), D35.3 (DIN)
unnamed: D35.1 (DOUT), D36.3 (DIN)
unnamed: D36.1 (DOUT), D37.3 (DIN)
unnamed: D37.1 (DOUT), D38.3 (DIN)
unnamed: D38.1 (DOUT), D39.3 (DIN)
unnamed: D39.1 (DOUT), D40.3 (DIN)
unnamed: D40.1 (DOUT), D41.3 (DIN)
unnamed: D41.1 (DOUT), D42.3 (DIN)
unnamed: D42.1 (DOUT), D43.3 (DIN)
unnamed: D43.1 (DOUT), D44.3 (DIN)
unnamed: M1.1 (1A), U1.13 (AO1)
unnamed: M1.2 (1B), U1.11 (AO2)
unnamed: M1.3 (2A), U1.10 (BO1)
unnamed: M1.4 (2B), U1.8 (BO2)

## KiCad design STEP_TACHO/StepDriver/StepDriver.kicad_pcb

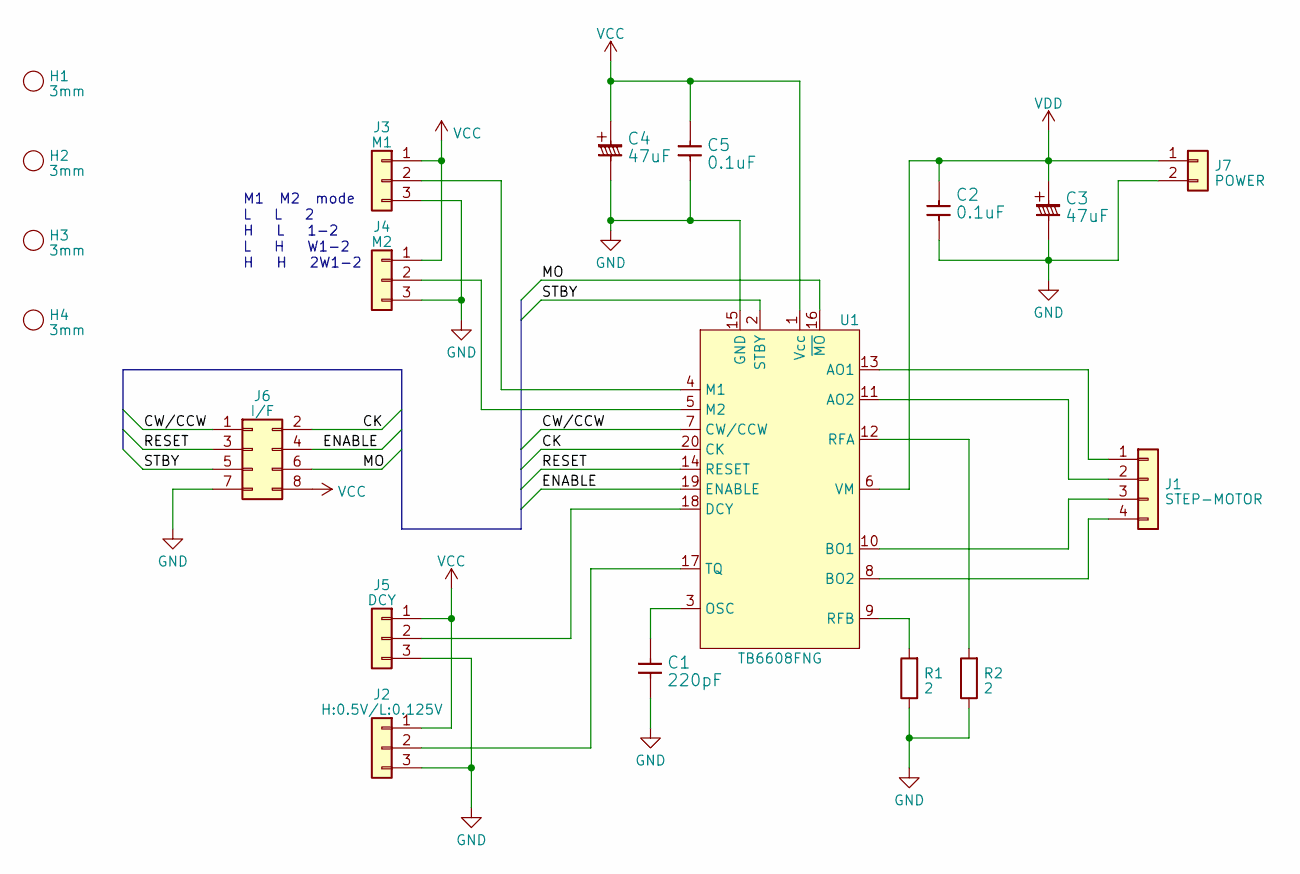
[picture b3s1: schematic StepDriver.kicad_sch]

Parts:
C1: 220pF; C_0603_1608Metric_Pad1.08x0.95mm_HandSolder
C2, C5: 0.1uF; C_0603_1608Metric_Pad1.08x0.95mm_HandSolder
C3, C4: 47uF; CP_Elec_6.3x5.4
H1, H2, H3, H4: 3mm; Hole3mm
J1: STEP-MOTOR; JST_EH_B4B-EH-A_1x04_P2.50mm_Vertical
J2: H:0.5V/L:0.125V; PinHeader_1x03_P2.54mm_Vertical
J3: M1; PinHeader_1x03_P2.54mm_Vertical
J4: M2; PinHeader_1x03_P2.54mm_Vertical
J5: DCY; PinHeader_1x03_P2.54mm_Vertical
J6: I/F; IDC-Header_2x04_P2.54mm_Vertical
J7: POWER; JST_EH_B2B-EH-A_1x02_P2.50mm_Vertical
R1, R2: 2; R_Box_L8.4mm_W2.5mm_P5.08mm
U1: TB6608FNG; SSOP-20_4.4x6.5mm_P0.65mm

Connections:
/CK: J6.2, U1.20 (CK)
/CW/CCW: J6.1, U1.7 (CW/CCW)
/ENABLE: J6.4, U1.19 (ENABLE)
/MO: J6.6, U1.16 (~MO)
/RESET: J6.3, U1.14 (RESET)
/STBY: J6.5, U1.2 (STBY)
GND: C1.1, C2.1, C3.2, C4.2, C5.1, J2.3, J3.3, J4.3, J5.3, J6.7, J7.2, R1.1, R2.1, U1.15 (GND)
unnamed: J1.1, U1.13 (AO1)
unnamed: J1.2, U1.11 (AO2)
unnamed: J1.3, U1.10 (BO1)
unnamed: J1.4, U1.8 (BO2)
unnamed: J2.2, U1.17 (TQ)
unnamed: J3.2, U1.4 (M1)
unnamed: J4.2, U1.5 (M2)
unnamed: J5.2, U1.18 (DCY)
unnamed: C1.2, U1.3 (OSC)
unnamed: R2.2, U1.12 (RFA)
unnamed: R1.2, U1.9 (RFB)
VCC: C4.1, C5.2, J2.1, J3.1, J4.1, J5.1, J6.8, U1.1 (Vcc)
VDD: C2.2, C3.1, J7.1, U1.6 (VM)

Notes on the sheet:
M1 M2 mode L L 2 H L 1-2 L H W1-2 H H 2W1-2

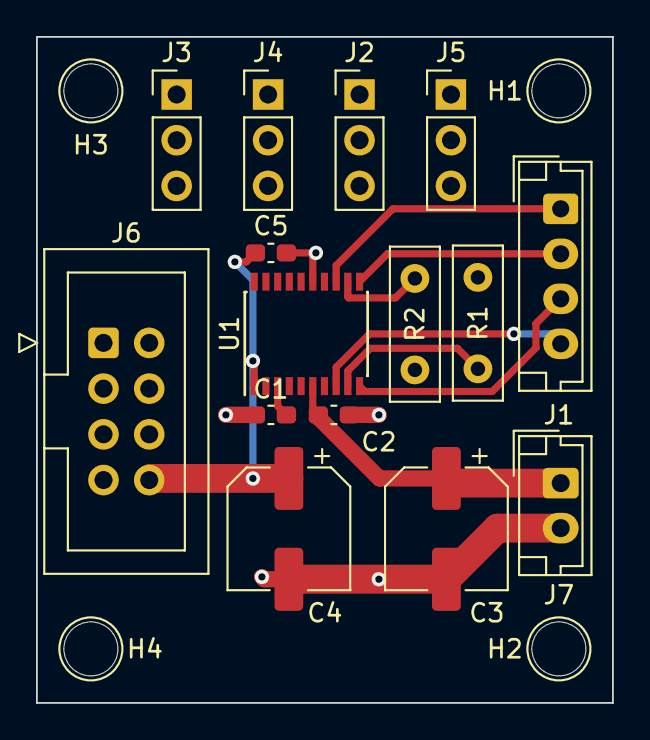
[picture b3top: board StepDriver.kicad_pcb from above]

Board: 2 copper layers, 32.0 x 37.0 mm, 19 parts (0 on the bottom side), 20 nets.

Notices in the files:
README.md:
Copyright (c) 2017 2019, Hiramatsu Kunihito
All rights reserved.
Redistribution and use in source and binary forms, with or without
modification, are permitted provided that the following conditions are met:
Redistributions of source code must retain the above copyright notice,
this list of conditions and the following disclaimer.
Redistributions in binary form must reproduce the above copyright notice,
this list of conditions and the following disclaimer in the documentation
and/or other materials provided with the distribution.
Neither the name of the
